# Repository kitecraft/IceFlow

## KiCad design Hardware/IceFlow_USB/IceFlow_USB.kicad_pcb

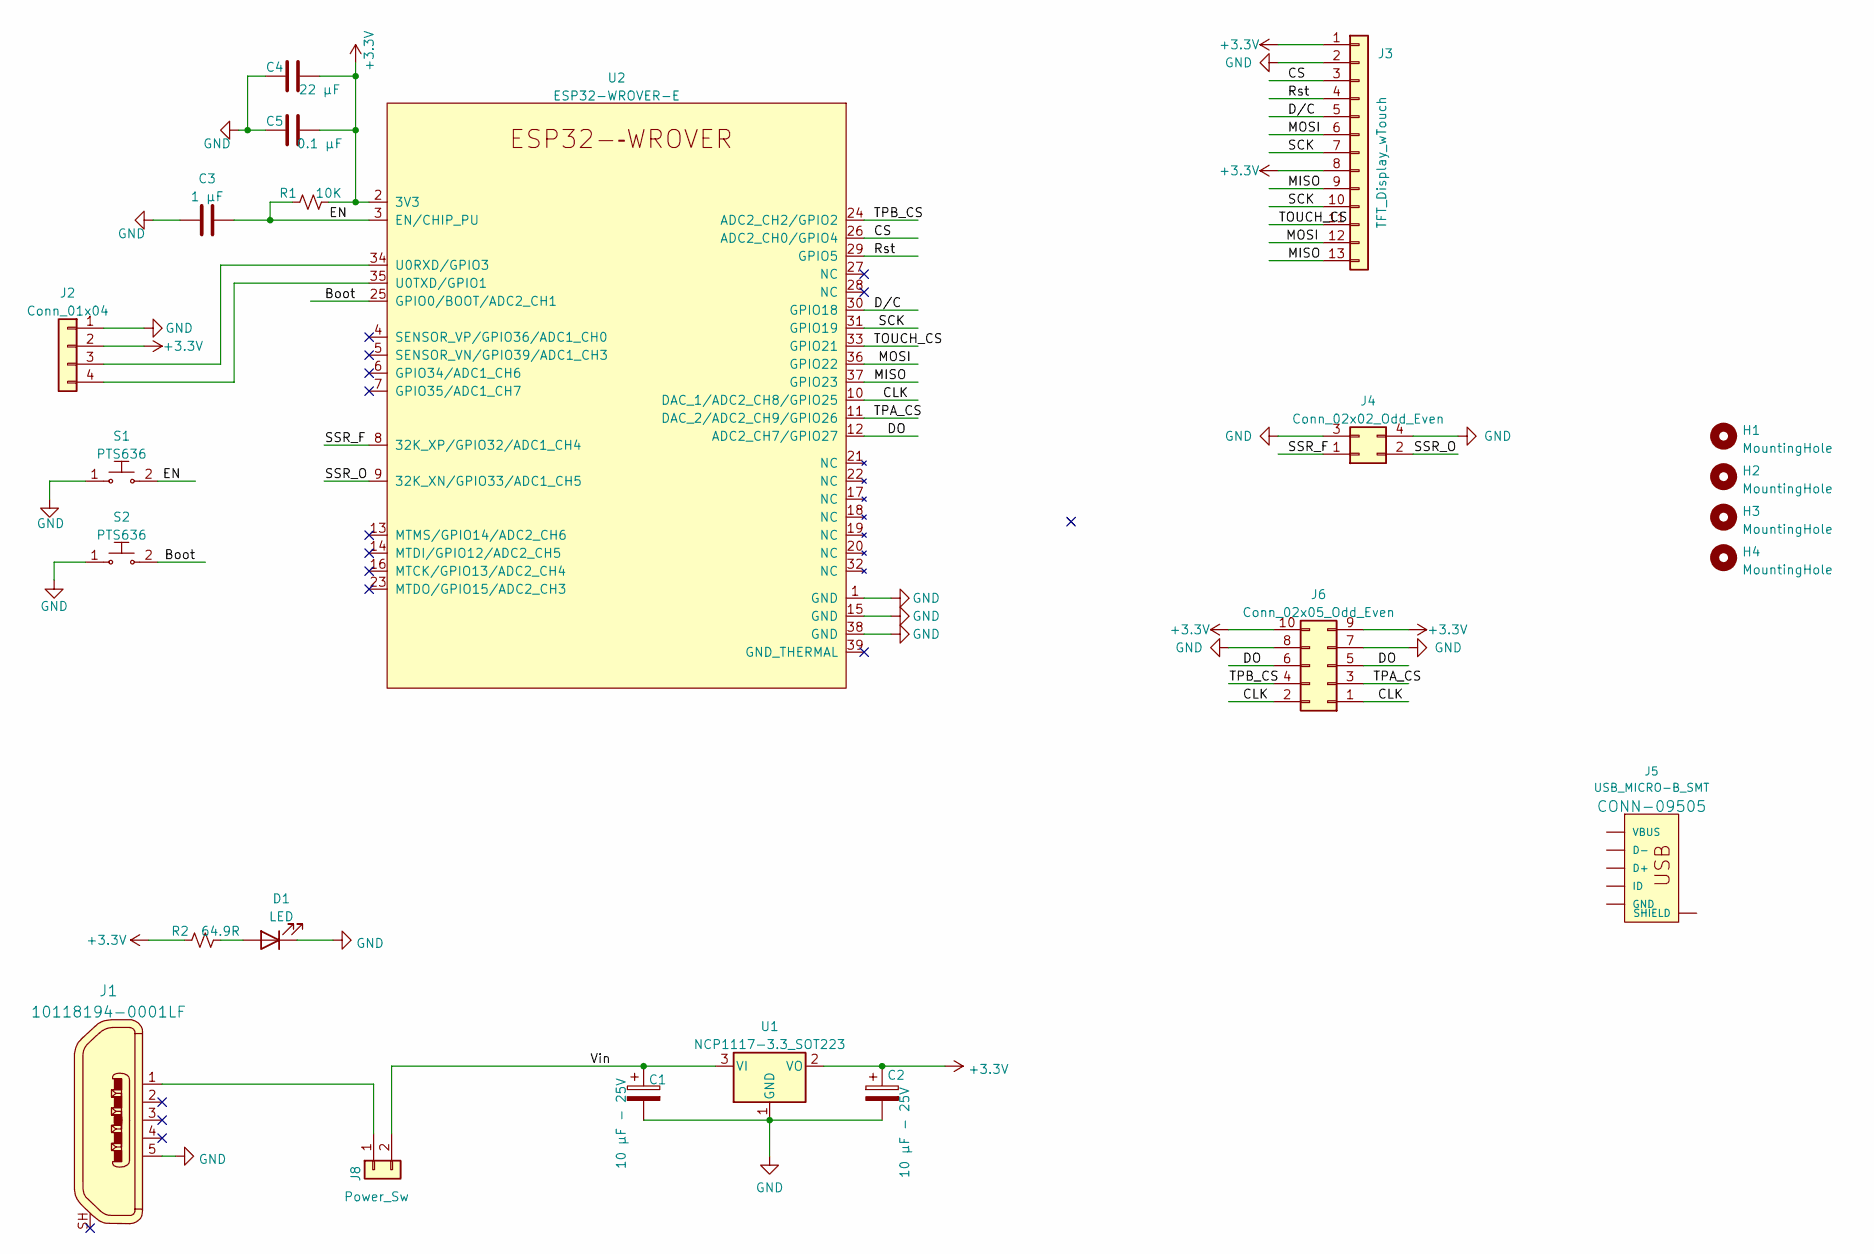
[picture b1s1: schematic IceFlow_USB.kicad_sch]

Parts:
C1, C2: 10 µF - 25V; CP_Elec_4x5.7
C3: 1 µF; C_0805_2012Metric_Pad1.18x1.45mm_HandSolder
C4: 22 µF; C_0805_2012Metric_Pad1.18x1.45mm_HandSolder
C5: 0.1 µF; C_0805_2012Metric_Pad1.18x1.45mm_HandSolder
D1: LED; LED_1206_3216Metric_Pad1.42x1.75mm_HandSolder
H1, H2, H3, H4: MountingHole; MountingHole_3.2mm_M3_DIN965
J1: 10118194-0001LF; USB_Micro_B_Female_10118194-0001LF; MPN 10118194-0001LF; Digi-Key_PN 609-4618-1-ND
J2: Conn_01x04; PinHeader_1x04_P2.54mm_Horizontal
J3: TFT_Display_wTouch; PinHeader_1x13_P2.54mm_Vertical
J4: Conn_02x02_Odd_Even; PinHeader_2x02_P2.54mm_Horizontal
J5: USB_MICRO-B_SMT; USB_Micro_B_Female_10118194-0001LF
J6: Conn_02x05_Odd_Even; PinHeader_2x05_P2.54mm_Horizontal
J8: Power_Sw; PinHeader_1x02_P2.54mm_Horizontal
R1: 10K; R_0805_2012Metric_Pad1.20x1.40mm_HandSolder
R2: 64.9R; R_1206_3216Metric_Pad1.30x1.75mm_HandSolder
S1, S2: PTS636; TACTILE_SWITCH_SMD_6.0X3.5MM; MPN GPTS203211B; Digi-Key_PN CW181-ND
U1: NCP1117-3.3_SOT223; SOT-223-3_TabPin2
U2: ESP32-WROVER-E; ESP32-WROVER-E_No_Thermals

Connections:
+3V3: C2.1, C4.2, C5.2, J2.2, J3.1, J3.8, J6.9, J6.10, R1.2, R2.1, U1.2 (VO), U2.2 (3V3)
/Boot: S2.2, U2.25 (GPIO0/BOOT/ADC2_CH1)
/CLK: J6.1, J6.2, U2.10 (DAC_1/ADC2_CH8/GPIO25)
/CS: J3.3, U2.26 (ADC2_CH0/GPIO4)
/DO: J6.5, J6.6, U2.12 (ADC2_CH7/GPIO27)
/D/C: J3.5, U2.30 (GPIO18)
/EN: C3.2, R1.1, S1.2, U2.3 (EN/CHIP_PU)
/MISO: J3.9, J3.13, U2.37 (GPIO23)
/MOSI: J3.6, J3.12, U2.36 (GPIO22)
/Rst: J3.4, U2.29 (GPIO5)
/SCK: J3.7, J3.10, U2.31 (GPIO19)
/SSR_F: J4.1, U2.8 (32K_XP/GPIO32/ADC1_CH4)
/SSR_O: J4.2, U2.9 (32K_XN/GPIO33/ADC1_CH5)
/TOUCH_CS: J3.11, U2.33 (GPIO21)
/TPA_CS: J6.3, U2.11 (DAC_2/ADC2_CH9/GPIO26)
/TPB_CS: J6.4, U2.24 (ADC2_CH2/GPIO2)
/Vin: C1.1, J8.2, U1.3 (VI)
GND: C1.2, C2.2, C3.1, C4.1, C5.1, D1.1 (K), J1.5, J2.1, J3.2, J4.3, J4.4, J6.7, J6.8, S1.1, S2.1, U1.1 (GND), U2.1 (GND), U2.15 (GND), U2.38 (GND)
unnamed: D1.2 (A), R2.2
unnamed: J1.1, J8.1
unnamed: J2.3, U2.34 (U0RXD/GPIO3)
unnamed: J2.4, U2.35 (U0TXD/GPIO1)
unnamed: J5.MT1 (SHIELD), J5.MT2 (SHIELD), J5.P$1 (SHIELD), J5.P$2 (SHIELD)

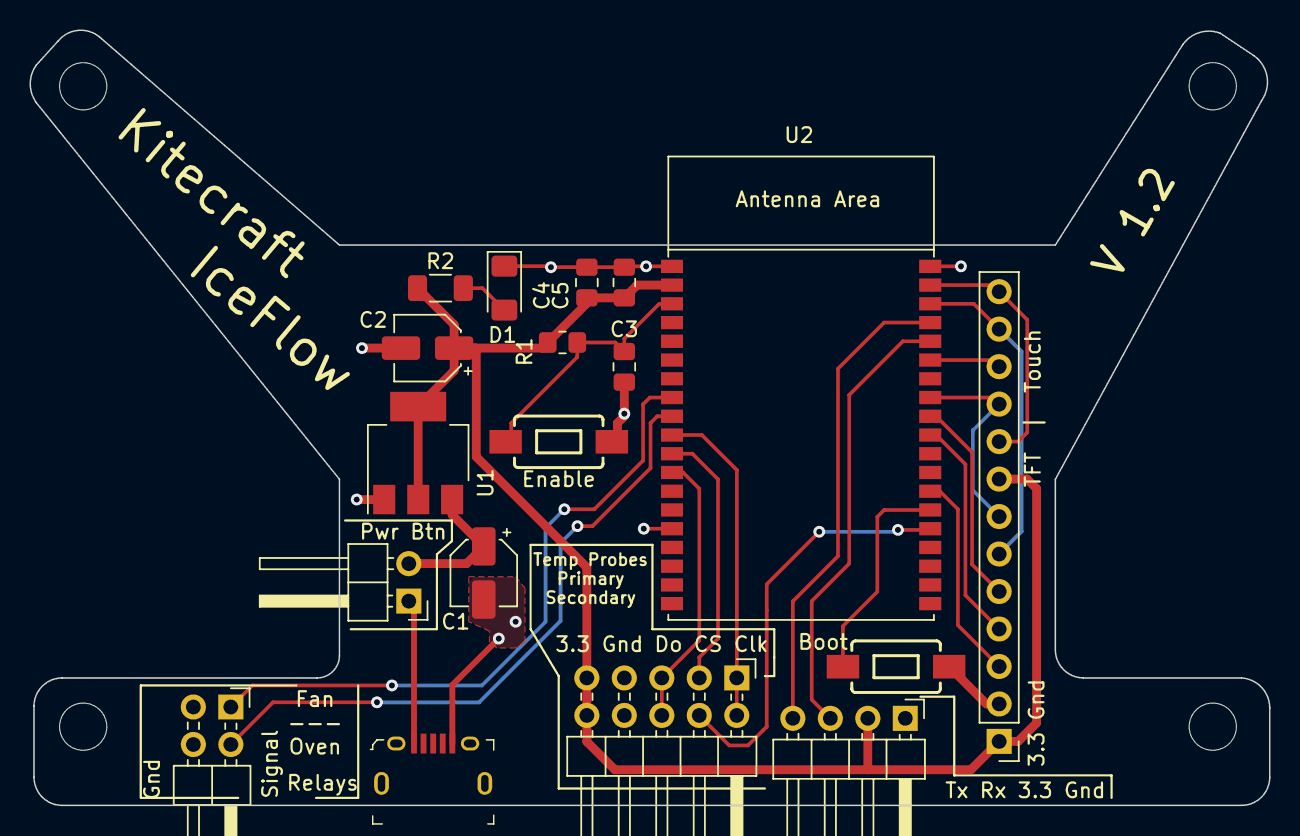
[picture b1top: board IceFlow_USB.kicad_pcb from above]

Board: 2 copper layers, 84.0 x 52.5 mm, 22 parts (0 on the bottom side), 22 nets.

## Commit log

2022-06-03 Seem to have working pid controller and pre-heat capabilities now.
2022-06-03 Added updateing local time from NTP
2022-06-04 Added the temperature panel and started a pre heat screen.
2022-06-04 Added Main Screen Header
2022-06-04 Create a panel base class for the panels.
2022-06-05 Moved several variables into global extern
2022-06-05 Saved project
2022-06-14 Working on the ESP32-S3 (ESP32-S3-DevKitC-1 N8R8)
2022-06-14 Removed commented code (from testing on the ESP32 with 8MB PSRAM)
2022-06-14 Update to printing out psram info at startup.
2022-06-14 Fixed bug preventing webserver from serving files.
2022-06-14 Updated to be able to redraw the entire screen with a single sprite.
2022-06-27 Tried a few things.
2022-06-29 last updates
2022-07-20 Starting over with a new DisplayManager
2022-07-20 More files
2022-07-21 Started on the new MainScreen.
2022-07-22 Added the sidebar and settings icon.
2022-07-23 Removed the WaitDMA() calls.
2022-07-23 First bit of the PopUpMenu widget.
2022-07-23 Added a PopUpMenu
2022-07-24 Adding header. Tweaked textbox to be able to auto adjust width according to text and use rounded box as well.
2022-07-24 Pretty much complete the Header. Also started on the ProfileManager.
2022-07-25 Added ProfileIcon
2022-07-26 Added a new Button widget and the ProfilesScreen
2022-07-28 Working on the Profile Screens profile list.
2022-07-29 Adding ScrollButtons and re-jiggered the sprites.
2022-07-29 Completed the profile file list including scroll bars and save/cancel buttons.
2022-07-30 Beginning to add the graph panel with double sprites in psram
2022-07-30 Added the grid and a new button in the header to show/hide the grid. Updated the headers on both both Main and Profile screens to use a large font, no text box for the device name.
2022-07-31 Completed adding the graphing panel which shows the profile.
2022-07-31 Add start of Oven Controller and Main Screen footer.
2022-08-04 Have the Temperatures legends working and the autoscaler working now.
2022-08-05 Adding the main graph sprite and good progress towards getting it working.
2022-08-05 Working graph with primary temperature.
2022-08-06 Pretty much complete now (without the tertiary temperature though).
2022-08-06 Final commit of GraphPanel and the Graph AutoScaler.
2022-08-06 Several bug fixes in the GraphAutoScaler as well as adding in support for secondary temperature autoscaling on the graph.
2022-08-06 Fixed a memory leak.
2022-08-06 Added ManualHeatIcon to main screen sidebar (not active yet)
2022-08-07 Added reflow icon (not functional yet)
2022-08-07 Added new PopUp Dialog for Start Manual Heat.
2022-08-07 Added a touched function to the textbox.
2022-08-08 Fixed option spacing on popup menu
2022-08-09 Added physical stop button. Turned on PID oven heater control.
2022-08-09 Added the tertiary temperature tracking to the main graph. added some new control commands and now the oven can better update the display.
2022-08-09 Added icon for when oven heaters are active
2022-08-10 Added a new NumberPad dialog box (should it be a widget?). Completed the dialogs and code for starting the manual heat. Except for storing and retrieving the value.
2022-08-11 Added new message box dialog class. Added a DO NOT EXCEED temperature and check it before sending. Pop up message box is target is over limit. :)
2022-08-11 Added edit button to profile screen.
2022-08-13 Much progress.
2022-08-13 Completed the Edit Profile screen except for the save and save as buttons.
2022-08-13 Addied saving profile on Profile Edit screen. Started on the keyboard dialog
2022-08-13 Added a working On-Screen Keyboard (landscape).
2022-08-14 Added the saving new profile to SPIFFS.
2022-08-14 Fix bug where delete button not appearing after copying the default profile.
2022-08-14 Added MAX31855 controller and now the primary temperature is a live reading.
2022-08-15 Updated pin mapping
2022-08-16 Updating pin mapping and thermocouple to use HSPI (at least for now)
2022-08-16 A couple funcs for starting AutoTune
2022-08-16 Added an AutoTune function based on Repetier v0.91 (from SeeMeCNC)
2022-08-17 Fixed some memory leaks and reworked some code to change my codeing style and help prevent further memory leaks.
2022-08-17 Added AutoTune to the MainScreen graph.
2022-08-17 Added disabling of icons in the sidebar by 'greying them out'
2022-08-18 Addeded new BaseScreen and Reflow screen.
2022-08-18 Converted MainScreen to use BaseScreen. Even saved 6KB of program space!
2022-08-18 Started on the Reflow Screens sidebar.
2022-08-19 Good progress on the reflow controller.
2022-08-20 Mostly completed the basics for all steps of the Reflow control and display. some bugs yet to fix.
2022-08-20 Fixed a bunch of bugs.
2022-08-20 Added the Target data box to the reflow screen sidebar.
2022-08-20 Adding a Reflow Complete message. Reflow seems to be working well. Just need to update the Main Screens RF icon to check if primaryTemperature is < 50C
2022-08-20 Added check for minimum temperature to starting a Reflow session. Couple new popup message boxes on main screen.
2022-08-21 Added a StopIcon to the sidebar and some logic around enable/disabling it.
2022-08-21 Can now show/hide the secondary and tertiary graph lines by touching the temperature text boxes in the footer. Nice!
2022-08-21 Gonna start on AutoTune
2022-08-21 Fixed the bugs in AutoTune()
2022-08-21 Fixed typo
2022-08-21 Added temperature select dialog to autotune startup.
2022-08-21 Fixed a bug where Iceflow would sometimes crash when starting AutoTune. Seems to be a in the Ovencontroller when the Reflow object wasn't cleaning up after itself when done. (or stopped).
2022-08-23 Added PID Edit dialog and mostly working. Did some other refactors that probably broked stuff. :(
2022-08-23 Added PID Editor dialog.
2022-08-24 Added a Save Required warning dialog. PID Editor and Auto Tune seem to be complete (as much as).
2022-08-24 Started on new Info Screen. Also playing with the theme colours a bit.
2022-08-25 Added network info display and ability to clear network info. Fixed a bug in messageBox where it wouldln't do a newline if \n was within the last lines length.
2022-08-25 Added info (settings) screen.
2022-08-26 Added the missing icons for the Message Box
2022-08-27 Added second thermocouple. It's a bit flaky due to the breadboard connections.
2022-08-30 Moved some pins around which fixed the temperature readings.
2022-09-02 Various attempts to get better readings from the MAX31855
2022-09-08 Finally figured out that the temperature sensor stability problems are related the 5V cicuitry.
2022-09-10 Fully working but no temperature sensors.
2022-09-10 try 2
2022-09-10 Fully working again.
2022-09-10 3rd try to get a fully working commit and push.
2022-09-10 Merge remote-tracking branch 'remotes/origin/015_Try2ForWorking' into HEAD
    # Conflicts:
    # Software/IceFlow/IceFlow/IceFlow.ino
    # Software/IceFlow/IceFlow/~AutoRecover.IceFlow.vcxproj
2022-09-10 Updated pin connections
2022-09-11 Everything seems to be working.
2022-09-16 Final testing and performed first reflow. All is good here.
2022-12-10 Updates to PCB
2022-12-11 PCB Updates
2022-12-11 PCB Update
2022-12-11 Files sent for fab
2023-01-11 Added second PCB with USB Power.
2023-01-28 Pin map changes
2023-01-31 Changed a couple of min-temps.
